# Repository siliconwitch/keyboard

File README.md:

# HWKB: Happy Witching Keyboard

A wireless, low-profile mechanical keyboard with a built-in touchpad. It uses a Unix layout in the style of the Happy Hacking Keyboard and works both at a desk and on the couch with a media center.

Layout inspired by the Happy Hacking Keyboard (HHKB), a trademark of PFU Limited. This project is not affiliated with or endorsed by PFU.

## What you get

If you build one, you get:

- A Bluetooth keyboard and touchpad in one device, running from a rechargeable battery.
- Kailh Choc low-profile switches under multicolor 3D-printed keycaps.
- A thin chassis made from two PCBs soldered into one 3.2 mm slab.
- Open hardware and firmware you can change.

[docs/product.md](docs/product.md) lists every feature.

## How the layout compares

Each image draws our keycaps over a dashed ghost of another keyboard, with both F keys centred on the same point.

### HHKB

Each letter key sits within 0.7 mm of its HHKB position across. Our rows are 0.55 mm closer together, and our modifiers are narrower to fit Choc keycap sizes.

### Apple Magic Keyboard, US layout

The letter keys use the same 19.0 mm key pitch and 18.5 mm row pitch as the Magic Keyboard, and each sits within 0.5 mm of its Magic Keyboard position across. Our keycaps are 1.5 mm wider and 1 mm deeper, so the gaps between them are narrower.

## Repository layout

| Directory    | Contents                                        |
| ------------ | ----------------------------------------------- |
| `docs`       | Product spec and images                         |
| `hardware`   | KiCad project                                   |
| `firmware`   | Firmware for the nRF54LM20A controller          |
| `production` | Gerbers and bill of materials for manufacturing |

## Status

Early design. Nothing is ready to build yet.

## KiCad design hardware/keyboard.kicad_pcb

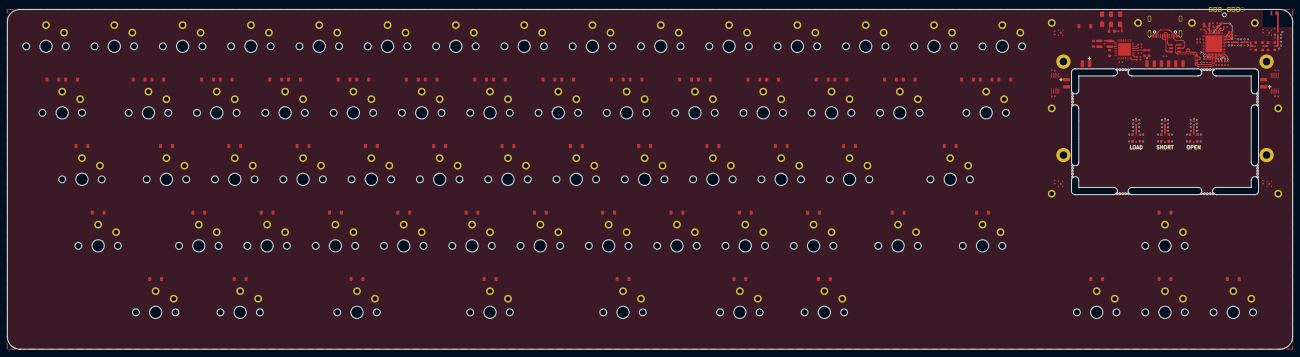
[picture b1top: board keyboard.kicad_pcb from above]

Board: 2 copper layers, 357.5 x 94.5 mm, 230 parts (1 on the bottom side), 148 nets.

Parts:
AE1: NN02-101
C1, C14: 10u; C-0402
C2, C3, C4, C13, C25, C26, C27, C28: 100n; C-0402
C5, C6, C7, C9, C12: 2.2u; C-0402
C8: 4.7u; C-0402
C10, C11, C29, C30, C31, C32, C33: 1u; C-0402
C15, C16: TBD; C-0402
C17, C19: 1.5p; C-0402
C18: 2.0p; C-0402
C20, C21, C22, C23, C24: 10u; C-0603
D1: SOT-23-6
D2, D3, D4, D5, D6, D7, D8, D9, D10, D11, D12, D13, D14, D15, D16, D17, D18, D19, D20, D21, D22, D23, D24, D25, D26, D27, D28, D29, D30, D31, D32, D33, D34, D35, D36, D37, D38, D39, D40, D41, D42, D43, D44, D45, D46, D47, D48, D49, D50, D51, D52, D53, D54, D55, D56, D57, D58, D59, D60, D61, D62, D63, D64, D65, D66, D67, D68: SOD-123
FB1: 120R; L-0402
J1: USB4105-GF-A
J2: BATTERY-SOLDER-PADS
J3, J4, J6, J7, J8: MM8130-2600
J5: ECV3-06
JH1, JH2, JH4, JH5, JH6, JH7, JH12, JH13: JOIN-HOLE
L1: 4.7u; L-0603
L2, L3: 2.2u; 0806
L4: TBD; L-0402
L5, L6: 2.0n; L-0402
L7: 2.7n; L-0402
M1, M2: LRA-SOLDER-PADS
MB1, MB2, MB3, MB4, MB5, MB6, MB7, MB8: MOUSE-BITE
R1, R2, R3, R5: 4.7k; R-0402
R4: 2.2R; R-0402
R6: 200R; R-0402
R7: 47k; R-0402
R8: 150k; R-0402
R9: 100R; R-0402
R10: 50R; R-0402
R11: 0R; R-0402
R12: R-0402
SO1, SO2, SO3, SO4: 9774010633R
SW1: CL-SB-22A
SW2, SW3, SW4, SW5, SW6, SW7, SW8, SW9, SW10, SW11, SW12, SW13, SW14, SW15, SW16, SW17, SW18, SW19, SW20, SW21, SW22, SW23, SW24, SW25, SW26, SW27, SW28, SW29, SW30, SW31, SW32, SW33, SW34, SW35, SW36, SW37, SW38, SW39, SW40, SW41, SW42, SW43, SW44, SW45, SW46, SW47, SW48, SW49, SW50, SW51, SW52, SW53, SW54, SW55, SW56, SW57, SW58, SW59, SW60, SW61, SW62, SW63, SW64, SW65, SW66, SW67: PG1350
U1: SMD-QFN32-1EP
U2: SMD-QFN52-1EP
U3, U4, U5, U6: HSFPAR004A
U7, U8: SMD-VSSOP10
U9: TOUCHPAD-SOLDER-PADS
Y1: 32MHz; CRYSTAL-4-PAD
Y2: 32.768kHz; CRYSTAL-2-PAD

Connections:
1.8V: C1.1, C2.1, C3.1, C4.1, C13.1, C14.1, C33.1, J5.1 (VCC), L2.2, R1.2, R2.2, R3.2, R5.2, U1.1 (VOUT1), U1.12 (VDDIO), U2.6 (VDD), U2.42 (VDD), U2.51 (VDD), U9.4 (VDDHI)
3.0V: C24.1, C25.2, C26.2, C27.2, C28.2, L3.2, U1.32 (VOUT2), U3.1 (VDD), U4.1 (VDD), U5.1 (VDD), U6.1 (VDD)
/COL0: SW2.1, SW11.1, SW20.1, SW29.1, SW38.1, SW47.1, SW55.1, SW64.1, U2.52 (P2.00)
/COL1: SW3.1, SW12.1, SW21.1, SW30.1, SW39.1, SW48.1, SW56.1, SW65.1, U2.1 (P2.01)
/COL2: SW4.1, SW13.1, SW22.1, SW31.1, SW40.1, SW49.1, SW57.1, SW66.1, U2.2 (P2.02)
/COL3: SW5.1, SW14.1, SW23.1, SW32.1, SW41.1, SW50.1, SW58.1, SW67.1, U2.3 (P2.03)
/COL4: SW6.1, SW15.1, SW24.1, SW33.1, SW42.1, SW51.1, SW59.1, U2.4 (P2.04)
/COL5: SW7.1, SW16.1, SW25.1, SW34.1, SW43.1, SW52.1, SW60.1, U2.5 (P2.05)
/COL6: SW8.1, SW17.1, SW26.1, SW35.1, SW44.1, SW53.1, SW61.1, U2.50 (P1.24)
/COL7: SW9.1, SW18.1, SW27.1, SW36.1, SW45.1, SW54.1, SW62.1, U2.11 (P1.01/NFC1)
/COL8: SW1.1 (A), SW10.1, SW19.1, SW28.1, SW37.1, SW46.1, SW63.1, U2.12 (P1.02/NFC2)
/FS1_N: U2.9 (P1.31/AIN1), U3.2 (V2)
/FS1_P: U2.10 (P1.00/AIN0), U3.4 (V1)
/FS2_N: U2.7 (P1.29/AIN3), U4.2 (V2)
/FS2_P: U2.8 (P1.30/AIN2), U4.4 (V1)
/FS3_N: U2.15 (P1.05/AIN5), U5.2 (V2)
/FS3_P: U2.16 (P1.06/AIN4), U5.4 (V1)
/FS4_N: U2.13 (P1.03/AIN7), U6.2 (V2)
/FS4_P: U2.14 (P1.04/AIN6), U6.4 (V1)
/HAPTIC_EN: U1.8 (GPIO1), U7.5 (EN), U8.5 (EN)
/I2C0_SCL: R1.1, U1.14 (SCL), U2.22 (P1.07/EXTREF), U7.2 (SCL), U9.5 (SCL)
/I2C0_SDA: R2.1, U1.13 (SDA), U2.23 (P1.08), U7.3 (SDA), U9.6 (SDA)
/I2C1_SCL: R3.1, U2.25 (P0.03), U8.2 (SCL)
/I2C1_SDA: R5.1, U2.26 (P0.04), U8.3 (SDA)
/RF_ANT: AE1.1 (A_1), C15.1, L4.1
/RF_FILTER1: C19.1, L6.2, L7.1
/RF_FILTER2: C18.1, L5.2, L6.1
/RF_FILTER_OUT: C17.1, J4.C, L5.1
/RF_LINK: J3.A, J4.A
/RF_LOAD: J6.C, R10.2
/RF_MATCH_IN: C16.1, J3.C, L4.2
/RF_NRF: L7.2, U2.34 (ANT)
/RF_OPEN: J8.C, R12.2
/RF_SHORT: J7.C, R11.2
/ROW0: D2.1 (K), D3.1 (K), D4.1 (K), D5.1 (K), D6.1 (K), D7.1 (K), D8.1 (K), D9.1 (K), D10.1 (K), U2.39 (P1.15)
/ROW1: D11.1 (K), D12.1 (K), D13.1 (K), D14.1 (K), D15.1 (K), D16.1 (K), D17.1 (K), D18.1 (K), D19.1 (K), U2.40 (P1.16)
/ROW2: D20.1 (K), D21.1 (K), D22.1 (K), D23.1 (K), D24.1 (K), D25.1 (K), D26.1 (K), D27.1 (K), D28.1 (K), U2.27 (P0.06)
/ROW3: D29.1 (K), D30.1 (K), D31.1 (K), D32.1 (K), D33.1 (K), D34.1 (K), D35.1 (K), D36.1 (K), D37.1 (K), U2.28 (P0.07)
/ROW4: D38.1 (K), D39.1 (K), D40.1 (K), D41.1 (K), D42.1 (K), D43.1 (K), D44.1 (K), D45.1 (K), D46.1 (K), U2.29 (P0.08)
/ROW5: D47.1 (K), D48.1 (K), D49.1 (K), D50.1 (K), D51.1 (K), D52.1 (K), D53.1 (K), D54.1 (K), U2.30 (P0.09)
/ROW6: D55.1 (K), D56.1 (K), D57.1 (K), D58.1 (K), D59.1 (K), D60.1 (K), D61.1 (K), D62.1 (K), D63.1 (K), U2.41 (P1.18)
/ROW7: D64.1 (K), D65.1 (K), D66.1 (K), D67.1 (K), D68.1 (K), U2.47 (P1.19)
/TP_NRST: U1.7 (GPIO0), U9.2 (NRST)
/TP_RDY: U2.24 (P1.09), U9.1 (RDY)
/USB_C_D+: D1.3 (I/O2), J1.A6 (D+), J1.B6 (D+)
/USB_C_D-: D1.1 (I/O1), J1.A7 (D-), J1.B7 (D-)
/USB_D+: D1.4 (I/O2), U2.19 (D+)
/USB_D-: D1.6 (I/O1), U2.20 (D-)
GND: C1.2, C2.2, C3.2, C4.2, C5.2, C6.2, C7.1, C8.2, C9.2, C10.2, C11.2, C12.2, C13.2, C14.2, C15.2, C16.2, C17.2, C18.2, C19.2, C21.2, C22.2, C23.2, C24.2, C25.1, C26.1, C27.1, C28.1, C29.2, C30.2, C31.2, C32.1, C33.2, D1.2 (GND), J1.A1 (GND), J1.A12 (GND), J1.B1 (GND), J1.B12 (GND), J1.SH (SHIELD), J2.2, J3.G, J4.G, J5.5 (GND), J6.G, J7.G, J8.G, R6.1, R7.1, R8.1, R10.1, R11.1, R12.1, SW1.6 (C), U1.2 (PVSS1), U1.6 (PVSS2), U1.18 (NTC), U1.28 (LSIN1/VINLDO1), U1.29 (LSOUT1/VOUTLDO1), U1.30 (LSIN2/VINLDO2), U1.31 (LSOUT2/VOUTLDO2), U1.33 (AVSS), U2.35 (VSS), U2.45 (VSS), U2.53 (VSS), U3.3 (GND), U3.5 (GND), U4.3 (GND), U4.5 (GND), U5.3 (GND), U5.5 (GND), U6.3 (GND), U6.5 (GND), U7.4 (IN/TRIG), U7.8 (GND), U8.4 (IN/TRIG), U8.8 (GND), U9.3 (GND), Y1.2 (G), Y1.4 (G)
unnamed: D2.2 (A), SW2.2
unnamed: D3.2 (A), SW3.2
unnamed: D4.2 (A), SW4.2
unnamed: D5.2 (A), SW5.2
unnamed: D6.2 (A), SW6.2
unnamed: D7.2 (A), SW7.2
unnamed: D8.2 (A), SW8.2
unnamed: D9.2 (A), SW9.2
unnamed: D10.2 (A), SW10.2
unnamed: D11.2 (A), SW11.2
unnamed: D12.2 (A), SW12.2
unnamed: D13.2 (A), SW13.2
unnamed: D14.2 (A), SW14.2
unnamed: D15.2 (A), SW15.2
unnamed: D16.2 (A), SW16.2
unnamed: D17.2 (A), SW17.2
unnamed: D18.2 (A), SW18.2
unnamed: D19.2 (A), SW19.2
unnamed: D20.2 (A), SW20.2
unnamed: D21.2 (A), SW21.2
unnamed: D22.2 (A), SW22.2
unnamed: D23.2 (A), SW23.2
unnamed: D24.2 (A), SW24.2
unnamed: D25.2 (A), SW25.2
unnamed: D26.2 (A), SW26.2
unnamed: D27.2 (A), SW27.2
unnamed: D28.2 (A), SW28.2
unnamed: D29.2 (A), SW29.2
unnamed: D30.2 (A), SW30.2
unnamed: D31.2 (A), SW31.2
unnamed: D32.2 (A), SW32.2
unnamed: D33.2 (A), SW33.2
unnamed: D34.2 (A), SW34.2
unnamed: D35.2 (A), SW35.2
unnamed: D36.2 (A), SW36.2
unnamed: D37.2 (A), SW37.2
unnamed: D38.2 (A), SW38.2
unnamed: D39.2 (A), SW39.2
unnamed: D40.2 (A), SW40.2
unnamed: D41.2 (A), SW41.2
unnamed: D42.2 (A), SW42.2
unnamed: D43.2 (A), SW43.2
unnamed: D44.2 (A), SW44.2
unnamed: D45.2 (A), SW45.2
unnamed: D46.2 (A), SW46.2
unnamed: D47.2 (A), SW47.2
unnamed: D48.2 (A), SW48.2
unnamed: D49.2 (A), SW49.2
unnamed: D50.2 (A), SW50.2
unnamed: D51.2 (A), SW51.2
unnamed: D52.2 (A), SW52.2
unnamed: D53.2 (A), SW53.2
unnamed: D54.2 (A), SW54.2
unnamed: D55.2 (A), SW55.2
unnamed: D56.2 (A), SW56.2
unnamed: D57.2 (A), SW57.2
unnamed: D58.2 (A), SW58.2
unnamed: D59.2 (A), SW59.2
unnamed: D60.2 (A), SW60.2
unnamed: D61.2 (A), SW61.2
unnamed: D62.2 (A), SW62.2
unnamed: D63.2 (A), SW63.2
unnamed: D64.2 (A), SW64.2
unnamed: D65.2 (A), SW65.2
unnamed: D66.2 (A), SW66.2
unnamed: D67.2 (A), SW67.2
unnamed: D68.2 (A), SW1.2 (B)
unnamed: J1.A5 (CC1), U1.23 (CC1)
unnamed: J1.B5 (CC2), U1.24 (CC2)
unnamed: J5.4 (SWCLK), U2.31 (SWDCLK)
unnamed: J5.2 (SWDIO), U2.32 (SWDIO)
unnamed: J5.3 (~RESET), U2.33 (~RESET)
unnamed: R9.1, SW1.4 (A)
unnamed: C20.2, SW1.5 (B)
unnamed: C20.1, R9.2, U1.15 (SHPHLD)
unnamed: L2.1, U1.3 (SW1)
unnamed: L3.1, U1.5 (SW2)
unnamed: R7.2, U1.17 (VSET1)
unnamed: R8.2, U1.16 (VSET2)
unnamed: L1.2, U2.43 (DCC)
unnamed: C6.1, C7.2, FB1.2, U2.36 (DECRF), U2.46 (DECA)
unnamed: C5.1, FB1.1, L1.1, U2.44 (DECD)
unnamed: C9.1, U2.18 (DECUSB)
unnamed: U2.48 (P1.20/XL1), Y2.1
unnamed: U2.49 (P1.21/XL2), Y2.2
unnamed: R6.2, U2.21 (TXRTUNE)
unnamed: C8.1, R4.1, U2.17 (VBUS)
unnamed: U2.37 (XC1), Y1.1
unnamed: U2.38 (XC2), Y1.3
unnamed: M1.1, U7.7 (OUT+)
unnamed: M1.2, U7.9 (OUT-)
unnamed: C31.1, U7.1 (REG)
unnamed: M2.1, U8.7 (OUT+)
unnamed: M2.2, U8.9 (OUT-)
unnamed: C32.2, U8.1 (REG)
V_{BATT}: C12.1, C29.1, C30.1, J2.1, U1.19 (VBAT), U7.6 (VDD/NC), U7.10 (VDD), U8.6 (VDD/NC), U8.10 (VDD)
V_{BUSOUT}: C11.1, R4.2, U1.22 (VBUSOUT)
V_{SYS}: C21.1, C22.1, C23.1, U1.4 (PVDD), U1.20 (VSYS)
V_{USB}: C10.1, D1.5 (VBUS), J1.A4 (VBUS), J1.A9 (VBUS), J1.B4 (VBUS), J1.B9 (VBUS), U1.21 (VBUS)
